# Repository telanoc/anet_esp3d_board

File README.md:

anet_esp3d_board
Copyright (c) 2018 by Pete Cervasio <cervasio@airmail.net>

License: Creative Commons Attribution-ShareAlike 4.0 International
(CC BY-SA 4.0)

This project implements a board to plug an ESP-01 running the ESP3d
software into the extra 10-pin connector on the Anet controller.

The transmit data of the ESP-01 is passed through a gated buffer, so that
GPIO 0 must be brought low for data to be sent to the printer.  This keeps
the ESP8266 startup noise out of the printer so it doesn't cough up a fur
ball.

You must remove two zero ohm resistors from the controller.  R52 and R53.
You must also either solder on a 6-pin jumper header or just solder jumper
wires in the BLE position of the USB/BLE pins.

Since GPIO 0 needs to be brought low, you must modify setup() of the ESP3d
sketch to add the following two lines:

void setup() {
    ... existing stuff

	pinMode(0, OUTPUT);
	digitalWrite(0, LOW);

	... more existing stuff

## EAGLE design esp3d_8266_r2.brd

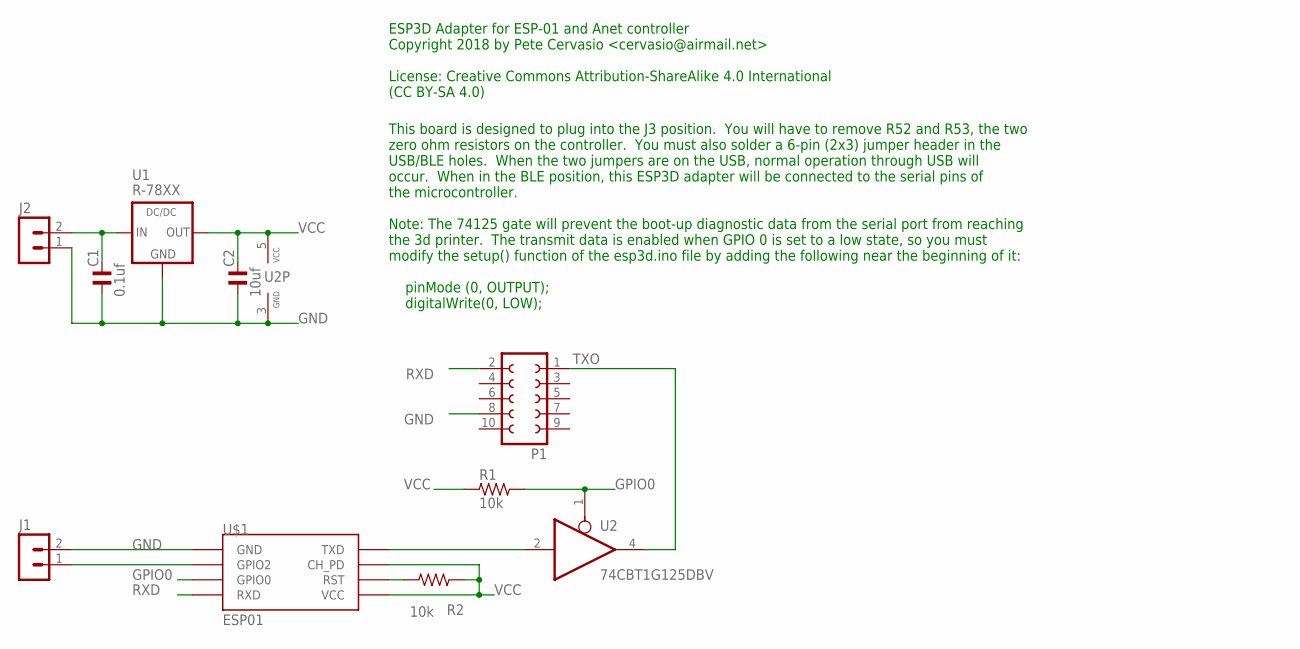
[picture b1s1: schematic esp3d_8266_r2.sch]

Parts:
C1: 0.1uf; C0805
C2: 10uf; C0805
J1, J2: MA02-1
P1: FE05-2
R1, R2: 10k; R0805
U1: R-78XX
U2: 74CBT1G125DBV; SOT23-5
U$1: ESP01

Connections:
GND: C1.1, C2.1, J1.2, J2.1, P1.8, U1.2 (GND), U2.3 (GND), U$1.GND
GPIO0: R1.2, U2.1 (OE), U$1.GPIO0
unnamed: U2.2 (I), U$1.TX (TXD)
unnamed: R2.2, U$1.RST
unnamed: J1.1, U$1.GPIO2
unnamed: C1.2, J2.2, U1.1 (IN)
RXD: P1.2, U$1.RX (RXD)
TXO: P1.1, U2.4 (O)
VCC: C2.2, R1.1, R2.1, U1.3 (OUT), U2.5 (VCC), U$1.CH_PD, U$1.VCC

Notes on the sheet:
ESP3D Adapter for ESP-01 and Anet controller Copyright 2018 by Pete Cervasio <cervasio@airmail.net> License: Creative Commons Attribution-ShareAlike 4.0 International (CC BY-SA 4.0)
This board is designed to plug into the J3 position. You will have to remove R52 and R53, the two zero ohm resistors on the controller. You must also solder a 6-pin (2x3) jumper header in the USB/BLE holes. When the two jumpers are on the USB, normal operation through USB will occur. When in the BL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

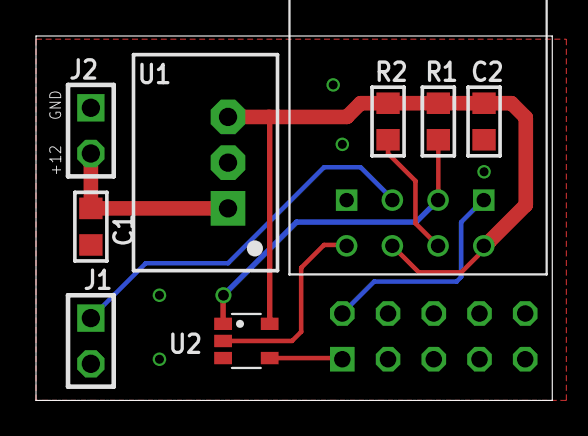
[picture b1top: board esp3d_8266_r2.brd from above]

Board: 2 copper layers, 28.7 x 20.2 mm, 10 parts (1 on the bottom side), 9 nets.

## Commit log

2018-04-17 Revision 2 of the board

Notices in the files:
esp3d_8266_r2.brd:
Copyright 2018 Pete Cervasio
License: (CC BY-SA 4.0)
parts and their libraries:
rc-master-smd: Copyright (C) 2007-2008, Bob Starr
